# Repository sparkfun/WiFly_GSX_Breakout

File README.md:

SparkFun WiFly GSX Breakout
========================================

[*SparkFun WiFly GSX Breakout (WRL-10050)*](https://www.sparkfun.com/products/10050)

This is a breakout board for the RN-131C WiFly GSX module, an ultra-low power 802.11b/g transceiver.
 This board breaks out all pins of the RN-131C to two 17-pin 0.1" pitch headers.
 
Repository Contents
-------------------

* **/Hardware** - Eagle design files (.brd, .sch)
* **/Production** - Production panel files (.brd)

Documentation
--------------
* **[Hookup Guide](https://learn.sparkfun.com/tutorials/wifly-shield-hookup-guide)** - Basic hookup guide for the WiFly module
* **[SparkFun Fritzing repo](https://github.com/sparkfun/Fritzing_Parts)** - Fritzing diagrams for SparkFun products.
* **[SparkFun 3D Model repo](https://github.com/sparkfun/3D_Models)** - 3D models of SparkFun products. 

License Information
-------------------
This product is _**open source**_! 

The **hardware** is released under [Creative Commons ShareAlike 4.0 International](https://creativecommons.org/licenses/by-sa/4.0/).

Please use, reuse, and modify these files as you see fit. Please maintain attribution to SparkFun Electronics and release anything derivative under the same license.

Distributed as-is; no warranty is given.

- Your friends at SparkFun.

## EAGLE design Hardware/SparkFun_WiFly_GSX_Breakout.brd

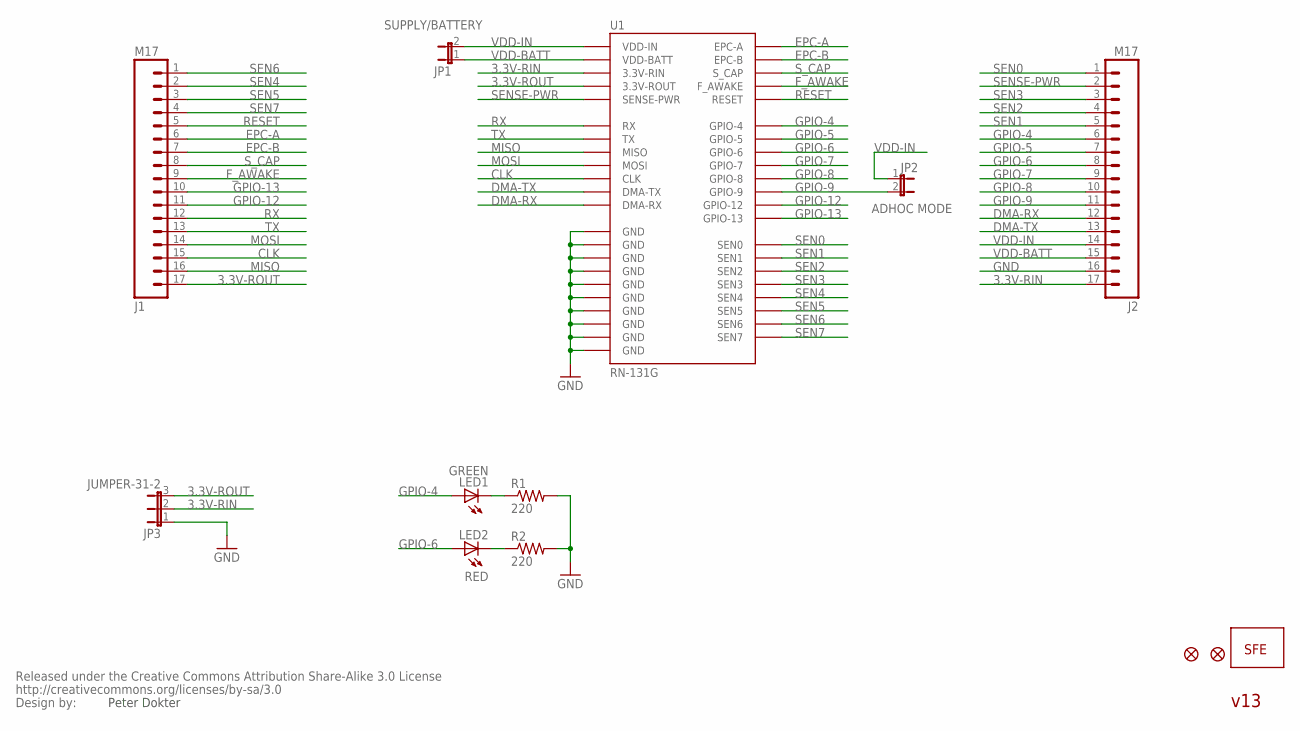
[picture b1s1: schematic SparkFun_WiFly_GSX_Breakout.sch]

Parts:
J1, J2: M17; 1X17
JP1, JP2: JUMPER-2SMD-NO; SJ_2S-NO
JP3: JUMPER-31-2; SJ_3_PASTE1&2
LED1: GREEN; LED-0603
LED2: RED; LED-0603
R1, R2: 220; 0402-RES
U1: RN-131G
U$1: LOGO-SFENEW; SFE-NEW-WEBLOGO
U$2, U$3: FIDUCIAL1X2; FIDUCIAL-1X2
U$4: CREATIVE_COMMONS

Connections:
3.3V-RIN: J2.17, JP3.2, U1.P$18 (3.3V-RIN)
3.3V-ROUT: J1.17, JP3.3, U1.P$17 (3.3V-ROUT)
CLK: J1.15, U1.P$15 (CLK)
DMA-RX: J2.12, U1.P$23 (DMA-RX)
DMA-TX: J2.13, U1.P$22 (DMA-TX)
EPC-A: J1.6, U1.P$6 (EPC-A)
EPC-B: J1.7, U1.P$7 (EPC-B)
F_AWAKE: J1.9, U1.P$9 (F_AWAKE)
GND: J2.16, JP3.1, R1.2, R2.2, U1.P$19 (GND), U1.P$36 (GND), U1.P$37 (GND), U1.P$38 (GND), U1.P$39 (GND), U1.P$40 (GND), U1.P$41 (GND), U1.P$42 (GND), U1.P$43 (GND), U1.P$44 (GND)
GPIO-4: J2.6, LED1.A, U1.P$29 (GPIO-4)
GPIO-5: J2.7, U1.P$28 (GPIO-5)
GPIO-6: J2.8, LED2.A, U1.P$27 (GPIO-6)
GPIO-7: J2.9, U1.P$26 (GPIO-7)
GPIO-8: J2.10, U1.P$25 (GPIO-8)
GPIO-9: J2.11, JP2.2, U1.P$24 (GPIO-9)
GPIO-12: J1.11, U1.P$11 (GPIO-12)
GPIO-13: J1.10, U1.P$10 (GPIO-13)
MISO: J1.16, U1.P$16 (MISO)
MOSI: J1.14, U1.P$14 (MOSI)
unnamed: LED2.C, R2.1
unnamed: LED1.C, R1.1
RESET: J1.5, U1.P$5 (RESET)
RX: J1.12, U1.P$12 (RX)
SEN0: J2.1, U1.P$34 (SEN0)
SEN1: J2.5, U1.P$30 (SEN1)
SEN2: J2.4, U1.P$31 (SEN2)
SEN3: J2.3, U1.P$32 (SEN3)
SEN4: J1.2, U1.P$2 (SEN4)
SEN5: J1.3, U1.P$3 (SEN5)
SEN6: J1.1, U1.P$1 (SEN6)
SEN7: J1.4, U1.P$4 (SEN7)
SENSE-PWR: J2.2, U1.P$33 (SENSE-PWR)
S_CAP: J1.8, U1.P$8 (S_CAP)
TX: J1.13, U1.P$13 (TX)
VDD-BATT: J2.15, JP1.1, U1.P$20 (VDD-BATT)
VDD-IN: J2.14, JP1.2, JP2.1, U1.P$21 (VDD-IN)

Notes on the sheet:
Peter Dokter
ADHOC MODE
SUPPLY/BATTERY
v13

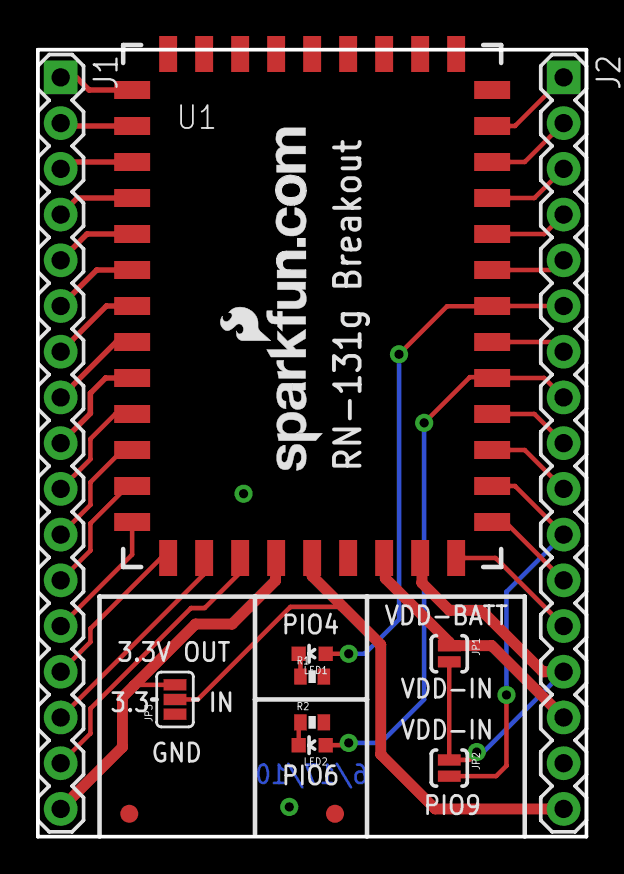
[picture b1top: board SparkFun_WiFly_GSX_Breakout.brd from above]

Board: 2 copper layers, 30.5 x 43.7 mm, 14 parts (0 on the bottom side), 36 nets.

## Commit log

2015-05-12 Adding hardware files

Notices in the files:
parts and their libraries:
SparkFun: Released under the Creative Commons Attribution Share-Alike 3.0 License
SparkFun: http://creativecommons.org/licenses/by-sa/3.0
